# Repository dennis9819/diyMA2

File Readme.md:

# Modular MIDI-Controller for GrandMA2 Software
*** This project only allows you to controll the grandMA2 Software via a hardware controller. You sitll need to buy a henuine grandMA Interface to unlock the reqired amount of universes. Please also be aware, that this is just a side-project of mine and is not designed for production use. Use the real stuff for that.***

The diyMA is an open source MIDI controller, strongly mimicking the onPC command and fader wing layout. It communicates with the onPC Software via MIDI. This limits the resolution of the faders to 7-Bit (0-127). In my case this is still enough.
I've designed three modules to construct your own modular controller

## The Modules
### Module I : Fader-Module
The fader module contains:
* 5 Executor-Faders (+3 Buttons each)
* 5 Button Executor
* Controller-Header (to connect to Controller-Module)
* 2 PCBs (1x Component-PCB, 1x Panel-PCB)

### Module 3 : Controller-Module
The fader module contains:
* MIDI-In (Passed through for daisy chaining)
* MIDI-Out
* Atmega8-16P @ 16MHz
* 1 ICSP Header (programming)
* +5V/+12V Power Supply

### Module 3 : Fader-Module
The fader module contains:
* 1 Master-Fader
* 69 Buttons
* MIDI-In (Passed through for daisy chaining)
* MIDI-Out
* +5V/+12V Power Supply
* Atmega8-16P @ 16MHz
* 1 Expansion Header (e.g.: more Executors)
* 1 ICSP Header (programming)
* 2 PCBs (1x Component-PCB, 1x Panel-PCB)

## Special-Parts
* https://de.aliexpress.com/item/1005003752250659.html?spm=a2g0o.order_list.order_list_main.105.3a725c5fgOUOYA&gatewayAdapt=glo2deu
* https://de.aliexpress.com/item/1005003201365793.html?spm=a2g0o.order_list.order_list_main.336.3a725c5fgOUOYA&gatewayAdapt=glo2deu
* https://de.aliexpress.com/item/32913352658.html?spm=a2g0o.order_list.order_list_main.321.3a725c5fgOUOYA&gatewayAdapt=glo2deu

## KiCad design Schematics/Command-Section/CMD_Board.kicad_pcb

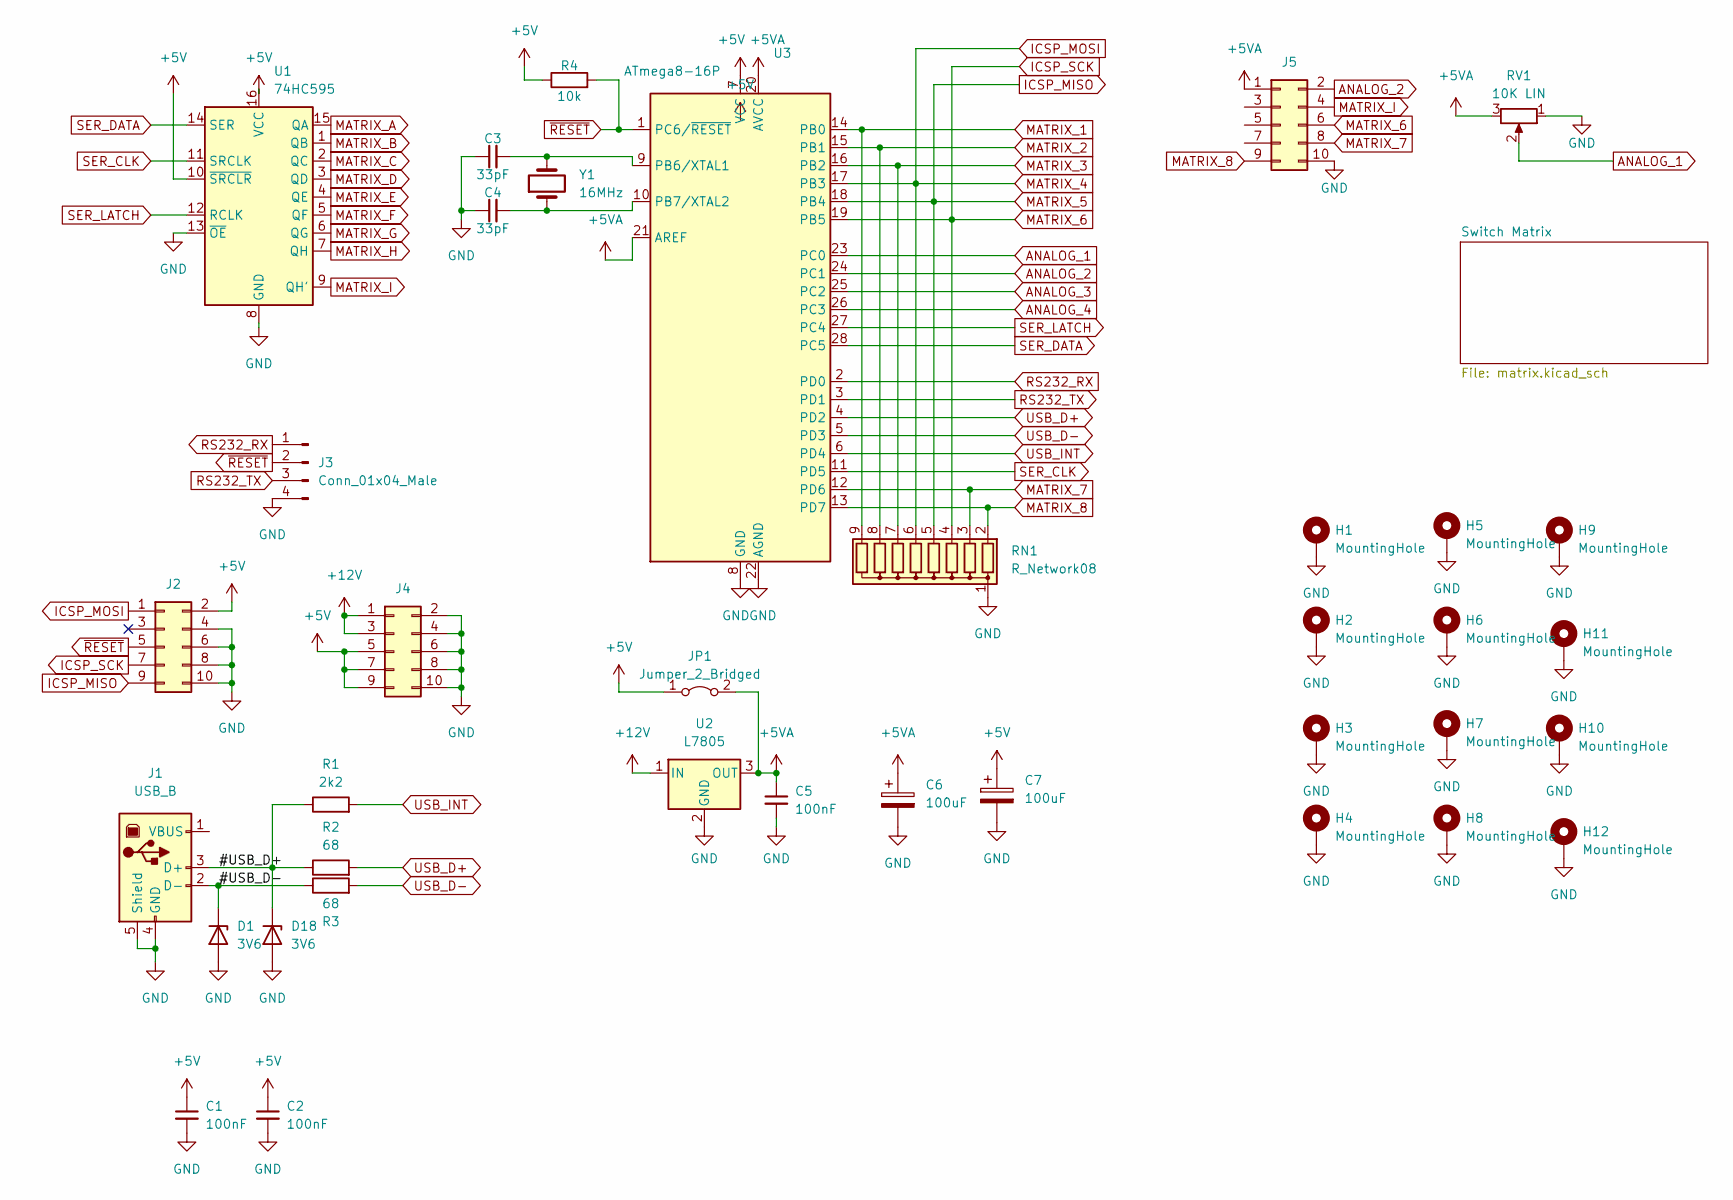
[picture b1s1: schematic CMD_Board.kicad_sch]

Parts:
C1, C2, C5: 100nF; C_Rect_L7.0mm_W2.0mm_P5.00mm
C3, C4: 33pF; C_Rect_L7.0mm_W2.0mm_P5.00mm
C6, C7: 100uF; CP_Radial_D8.0mm_P2.50mm
D1, D18: 3V6; D_DO-35_SOD27_P10.16mm_Horizontal
H1, H2, H3, H4, H5, H6, H7, H8, H9, H10, H11, H12: MountingHole; MountingHole_3.2mm_M3_DIN965_Pad
J1: USB_B; USB_B_Lumberg_2411_02_Horizontal
J2: Conn_02x05_Odd_Even; IDC-Header_2x05_P2.54mm_Vertical
J3: Conn_01x04_Male; JST_EH_B4B-EH-A_1x04_P2.50mm_Vertical
J4, J5: Conn_02x05_Odd_Even; IDC-Header_2x05_P2.54mm_Latch_Vertical
JP1: Jumper_2_Bridged; SolderJumper-2_P1.3mm_Bridged_Pad1.0x1.5mm
R1: 2k2; R_Axial_DIN0207_L6.3mm_D2.5mm_P7.62mm_Horizontal
R2, R3: 68; R_Axial_DIN0207_L6.3mm_D2.5mm_P7.62mm_Horizontal
R4: 10k; R_Axial_DIN0204_L3.6mm_D1.6mm_P2.54mm_Vertical
RN1: R_Network08; R_Array_SIP9
RV1: 10K LIN; RS60N12-LIN10K
U1: 74HC595; DIP-16_W7.62mm_Socket_LongPads
U2: L7805; TO-220-3_Horizontal_TabDown
U3: ATmega8-16P; DIP-28_W7.62mm_LongPads
Y1: 16MHz; Crystal_HC18-U_Vertical

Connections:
+5V: C1.1, C2.1, C7.1, J2.2, J4.5, J4.7, J4.9, JP1.1 (A), R4.1, U1.10 (~SRCLR), U1.16 (VCC), U3.7 (VCC)
+5VA: C5.1, C6.1, J5.1, JP1.2 (B), RV1.3, U2.3 (OUT), U3.20 (AVCC), U3.21 (AREF)
+12V: J4.1, J4.3, U2.1 (IN)
/#USB_D+: D18.1 (K), J1.3 (D+), R1.1, R2.1
/#USB_D-: D1.1 (K), J1.2 (D-), R3.1
ANALOG_1: RV1.2, U3.23 (PC0)
ANALOG_2: J5.2, U3.24 (PC1)
ANALOG_3: U3.25 (PC2)
ANALOG_4: U3.26 (PC3)
GND: C1.2, C2.2, C3.1, C4.1, C5.2, C6.2, C7.2, D1.2 (A), D18.2 (A), H1.1, H2.1, H3.1, H4.1, H5.1, H6.1, H7.1, H8.1, H9.1, H10.1, H11.1, H12.1, J1.4 (GND), J1.5 (Shield), J2.4, J2.6, J2.8, J2.10, J3.4, J4.2, J4.4, J4.6, J4.8, J4.10, J5.10, RN1.1 (common), RV1.1, U1.8 (GND), U1.13 (~OE), U2.2 (GND), U3.8 (GND), U3.22 (AGND); also elsewhere on the board
ICSP_MISO: J2.9, RN1.5 (R4), U3.18 (PB4); also elsewhere on the board
ICSP_MOSI: J2.1, RN1.6 (R5), U3.17 (PB3); also elsewhere on the board
ICSP_SCK: J2.7, J5.6, RN1.4 (R3), U3.19 (PB5); also elsewhere on the board
MATRIX_1: RN1.9 (R8), U3.14 (PB0); also elsewhere on the board
MATRIX_2: RN1.8 (R7), U3.15 (PB1); also elsewhere on the board
MATRIX_3: RN1.7 (R6), U3.16 (PB2); also elsewhere on the board
MATRIX_7: J5.8, RN1.3 (R2), U3.12 (PD6); also elsewhere on the board
MATRIX_8: J5.9, RN1.2 (R1), U3.13 (PD7); also elsewhere on the board
MATRIX_A: U1.15 (QA); also elsewhere on the board
MATRIX_B: U1.1 (QB); also elsewhere on the board
MATRIX_C: U1.2 (QC); also elsewhere on the board
MATRIX_D: U1.3 (QD); also elsewhere on the board
MATRIX_E: U1.4 (QE); also elsewhere on the board
MATRIX_F: U1.5 (QF); also elsewhere on the board
MATRIX_G: U1.6 (QG); also elsewhere on the board
MATRIX_H: U1.7 (QH); also elsewhere on the board
MATRIX_I: J5.4, U1.9 (QH'); also elsewhere on the board
unnamed: C3.2, U3.9 (PB6/XTAL1), Y1.2
unnamed: C4.2, U3.10 (PB7/XTAL2), Y1.1
RS232_RX: J3.1, U3.2 (PD0)
RS232_TX: J3.3, U3.3 (PD1)
SER_CLK: U1.11 (SRCLK), U3.11 (PD5)
SER_DATA: U1.14 (SER), U3.28 (PC5)
SER_LATCH: U1.12 (RCLK), U3.27 (PC4)
USB_D+: R2.2, U3.4 (PD2)
USB_D-: R3.2, U3.5 (PD3)
USB_INT: R1.2, U3.6 (PD4)
~RESET: J2.5, J3.2, R4.2, U3.1 (PC6/~RESET)

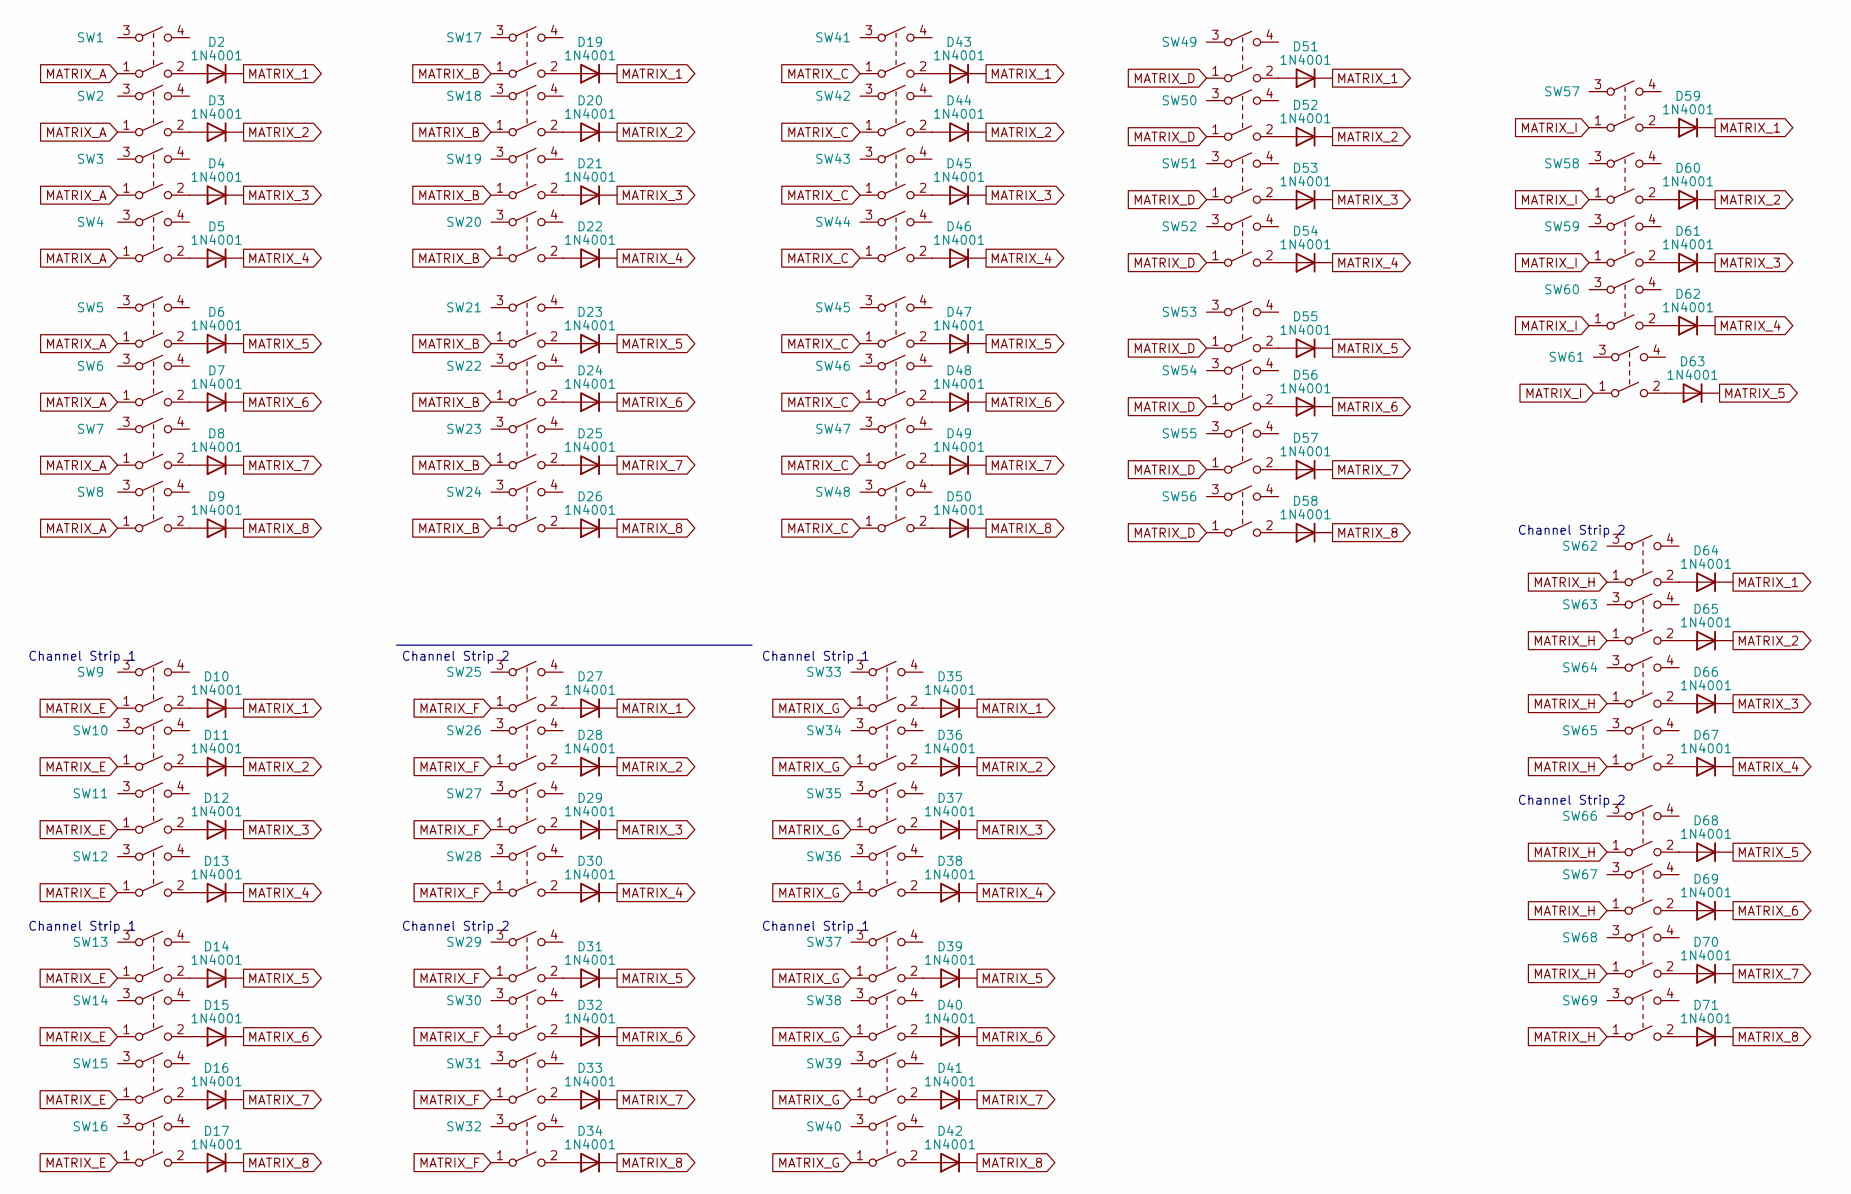
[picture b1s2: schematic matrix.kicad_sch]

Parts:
D2, D3, D4, D5, D6, D7, D8, D9, D10, D11, D12, D13, D14, D15, D16, D17, D19, D20, D21, D22, D23, D24, D25, D26, D27, D28, D29, D30, D31, D32, D33, D34, D35, D36, D37, D38, D39, D40, D41, D42, D43, D44, D45, D46, D47, D48, D49, D50, D51, D52, D53, D54, D55, D56, D57, D58, D59, D60, D61, D62, D63, D64, D65, D66, D67, D68, D69, D70, D71: 1N4001; D_DO-41_SOD81_P10.16mm_Horizontal
SW1, SW2, SW3, SW4, SW5, SW6, SW7, SW8, SW9, SW10, SW11, SW12, SW13, SW14, SW15, SW16, SW17, SW18, SW19, SW20, SW21, SW22, SW23, SW24, SW25, SW26, SW27, SW28, SW29, SW30, SW31, SW32, SW33, SW34, SW35, SW36, SW37, SW38, SW39, SW40, SW41, SW42, SW43, SW44, SW45, SW46, SW47, SW48, SW49, SW50, SW51, SW52, SW53, SW54, SW55, SW56, SW57, SW58, SW59, SW60, SW61, SW62, SW63, SW64, SW65, SW66, SW67, SW68, SW69: Switch_SW_DPST; SW_Cherry_MX_PCB_1.00u

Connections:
ICSP_MISO: D6.1 (K), D14.1 (K), D23.1 (K), D31.1 (K), D39.1 (K), D47.1 (K), D55.1 (K), D63.1 (K), D68.1 (K); also elsewhere on the board
ICSP_MOSI: D5.1 (K), D13.1 (K), D22.1 (K), D30.1 (K), D38.1 (K), D46.1 (K), D54.1 (K), D62.1 (K), D67.1 (K); also elsewhere on the board
ICSP_SCK: D7.1 (K), D15.1 (K), D24.1 (K), D32.1 (K), D40.1 (K), D48.1 (K), D56.1 (K), D69.1 (K); also elsewhere on the board
MATRIX_1: D2.1 (K), D10.1 (K), D19.1 (K), D27.1 (K), D35.1 (K), D43.1 (K), D51.1 (K), D59.1 (K), D64.1 (K); also elsewhere on the board
MATRIX_2: D3.1 (K), D11.1 (K), D20.1 (K), D28.1 (K), D36.1 (K), D44.1 (K), D52.1 (K), D60.1 (K), D65.1 (K); also elsewhere on the board
MATRIX_3: D4.1 (K), D12.1 (K), D21.1 (K), D29.1 (K), D37.1 (K), D45.1 (K), D53.1 (K), D61.1 (K), D66.1 (K); also elsewhere on the board
MATRIX_7: D8.1 (K), D16.1 (K), D25.1 (K), D33.1 (K), D41.1 (K), D49.1 (K), D57.1 (K), D70.1 (K); also elsewhere on the board
MATRIX_8: D9.1 (K), D17.1 (K), D26.1 (K), D34.1 (K), D42.1 (K), D50.1 (K), D58.1 (K), D71.1 (K); also elsewhere on the board
MATRIX_A: SW1.1, SW2.1, SW3.1, SW4.1, SW5.1, SW6.1, SW7.1, SW8.1; also elsewhere on the board
MATRIX_B: SW17.1, SW18.1, SW19.1, SW20.1, SW21.1, SW22.1, SW23.1, SW24.1; also elsewhere on the board
MATRIX_C: SW41.1, SW42.1, SW43.1, SW44.1, SW45.1, SW46.1, SW47.1, SW48.1; also elsewhere on the board
MATRIX_D: SW49.1, SW50.1, SW51.1, SW52.1, SW53.1, SW54.1, SW55.1, SW56.1; also elsewhere on the board
MATRIX_E: SW9.1, SW10.1, SW11.1, SW12.1, SW13.1, SW14.1, SW15.1, SW16.1; also elsewhere on the board
MATRIX_F: SW25.1, SW26.1, SW27.1, SW28.1, SW29.1, SW30.1, SW31.1, SW32.1; also elsewhere on the board
MATRIX_G: SW33.1, SW34.1, SW35.1, SW36.1, SW37.1, SW38.1, SW39.1, SW40.1; also elsewhere on the board
MATRIX_H: SW62.1, SW63.1, SW64.1, SW65.1, SW66.1, SW67.1, SW68.1, SW69.1; also elsewhere on the board
MATRIX_I: SW57.1, SW58.1, SW59.1, SW60.1, SW61.1; also elsewhere on the board
unnamed: D2.2 (A), SW1.2
unnamed: D3.2 (A), SW2.2
unnamed: D4.2 (A), SW3.2
unnamed: D5.2 (A), SW4.2
unnamed: D6.2 (A), SW5.2
unnamed: D7.2 (A), SW6.2
unnamed: D8.2 (A), SW7.2
unnamed: D9.2 (A), SW8.2
unnamed: D10.2 (A), SW9.2
unnamed: D11.2 (A), SW10.2
unnamed: D12.2 (A), SW11.2
unnamed: D13.2 (A), SW12.2
unnamed: D14.2 (A), SW13.2
unnamed: D15.2 (A), SW14.2
unnamed: D16.2 (A), SW15.2
unnamed: D17.2 (A), SW16.2
unnamed: D19.2 (A), SW17.2
unnamed: D20.2 (A), SW18.2
unnamed: D21.2 (A), SW19.2
unnamed: D22.2 (A), SW20.2
unnamed: D23.2 (A), SW21.2
unnamed: D24.2 (A), SW22.2
unnamed: D25.2 (A), SW23.2
unnamed: D26.2 (A), SW24.2
unnamed: D27.2 (A), SW25.2
unnamed: D28.2 (A), SW26.2
unnamed: D29.2 (A), SW27.2
unnamed: D30.2 (A), SW28.2
unnamed: D31.2 (A), SW29.2
unnamed: D32.2 (A), SW30.2
unnamed: D33.2 (A), SW31.2
unnamed: D34.2 (A), SW32.2
unnamed: D35.2 (A), SW33.2
unnamed: D36.2 (A), SW34.2
unnamed: D37.2 (A), SW35.2
unnamed: D38.2 (A), SW36.2
unnamed: D39.2 (A), SW37.2
unnamed: D40.2 (A), SW38.2
unnamed: D41.2 (A), SW39.2
unnamed: D42.2 (A), SW40.2
unnamed: D43.2 (A), SW41.2
unnamed: D44.2 (A), SW42.2
unnamed: D45.2 (A), SW43.2
unnamed: D46.2 (A), SW44.2
unnamed: D47.2 (A), SW45.2
unnamed: D48.2 (A), SW46.2
unnamed: D49.2 (A), SW47.2
unnamed: D50.2 (A), SW48.2
unnamed: D51.2 (A), SW49.2
unnamed: D52.2 (A), SW50.2
unnamed: D53.2 (A), SW51.2
unnamed: D54.2 (A), SW52.2
unnamed: D55.2 (A), SW53.2
unnamed: D56.2 (A), SW54.2
unnamed: D57.2 (A), SW55.2
unnamed: D58.2 (A), SW56.2
unnamed: D59.2 (A), SW57.2
unnamed: D60.2 (A), SW58.2
unnamed: D61.2 (A), SW59.2
unnamed: D62.2 (A), SW60.2
unnamed: D63.2 (A), SW61.2
unnamed: D64.2 (A), SW62.2
unnamed: D65.2 (A), SW63.2
unnamed: D66.2 (A), SW64.2
unnamed: D67.2 (A), SW65.2
unnamed: D68.2 (A), SW66.2
unnamed: D69.2 (A), SW67.2
unnamed: D70.2 (A), SW68.2
unnamed: D71.2 (A), SW69.2

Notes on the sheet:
Channel Strip 2
Channel Strip 1

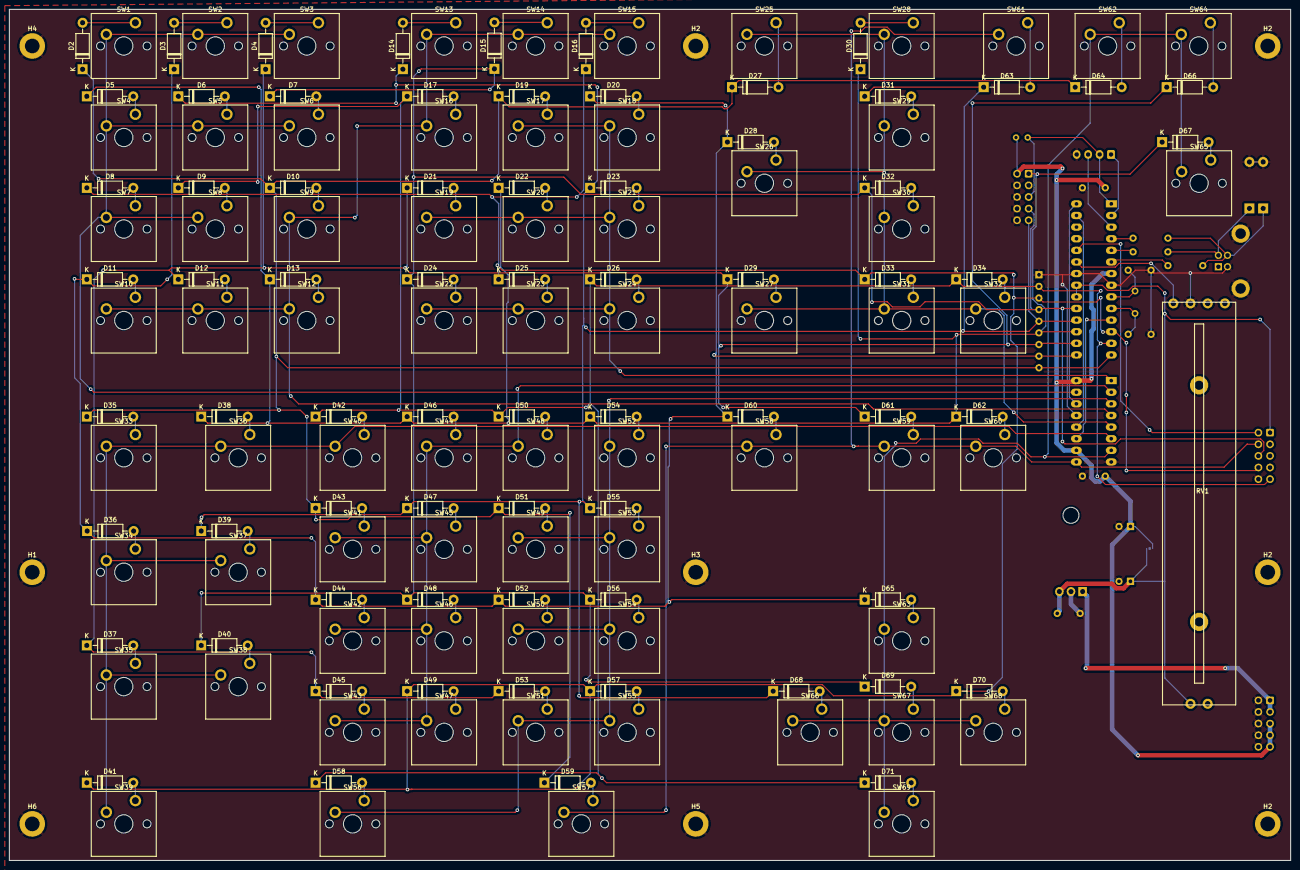
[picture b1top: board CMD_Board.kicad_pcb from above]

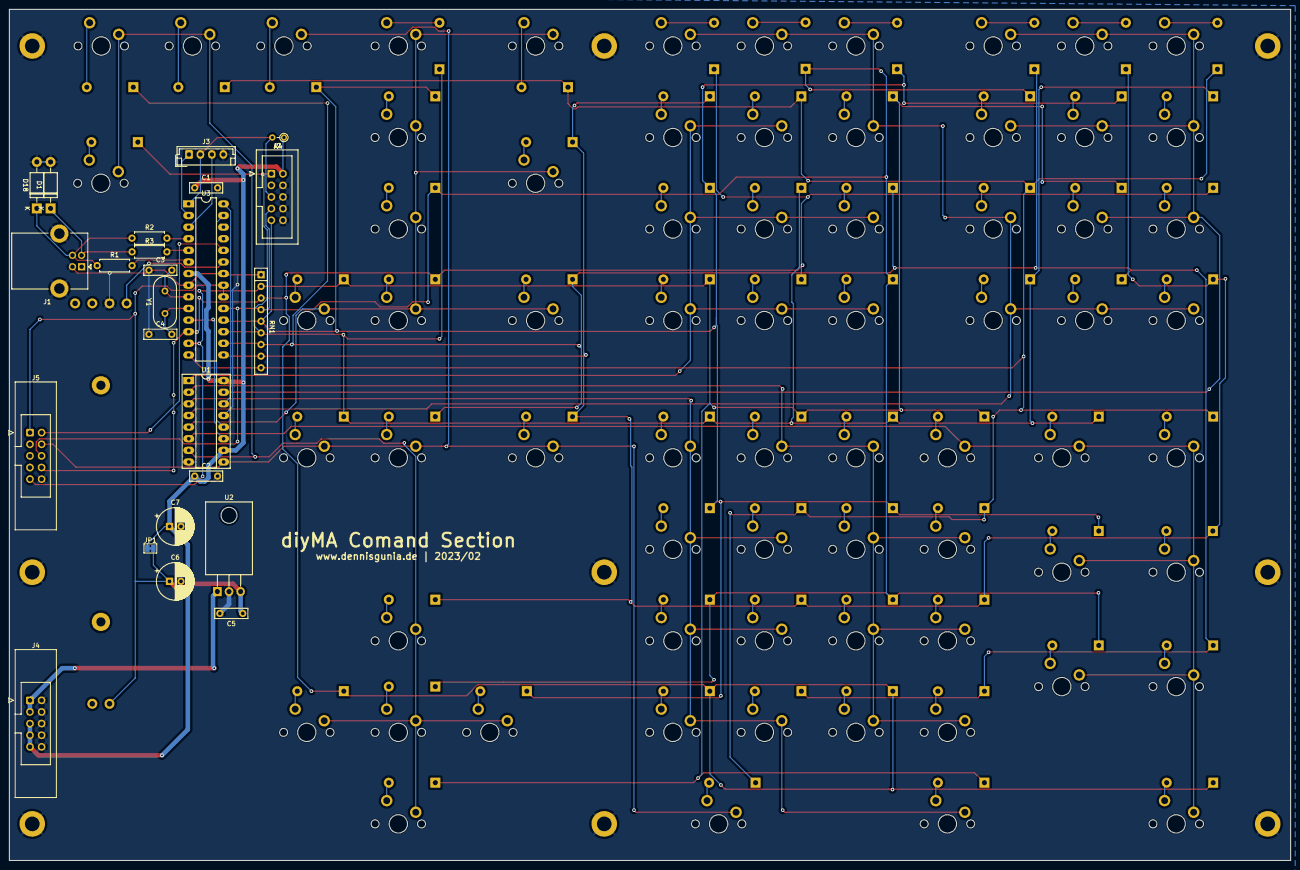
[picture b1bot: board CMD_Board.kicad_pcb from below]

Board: 2 copper layers, 280.0 x 186.0 mm, 172 parts (24 on the bottom side), 105 nets.

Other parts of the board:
H2#2, H2#3, H2#4: MountingHole; MountingHole_3.2mm_M3_DIN965_Pad

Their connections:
GND: H2#2.1, H2#3.1, H2#4.1; also elsewhere on the board

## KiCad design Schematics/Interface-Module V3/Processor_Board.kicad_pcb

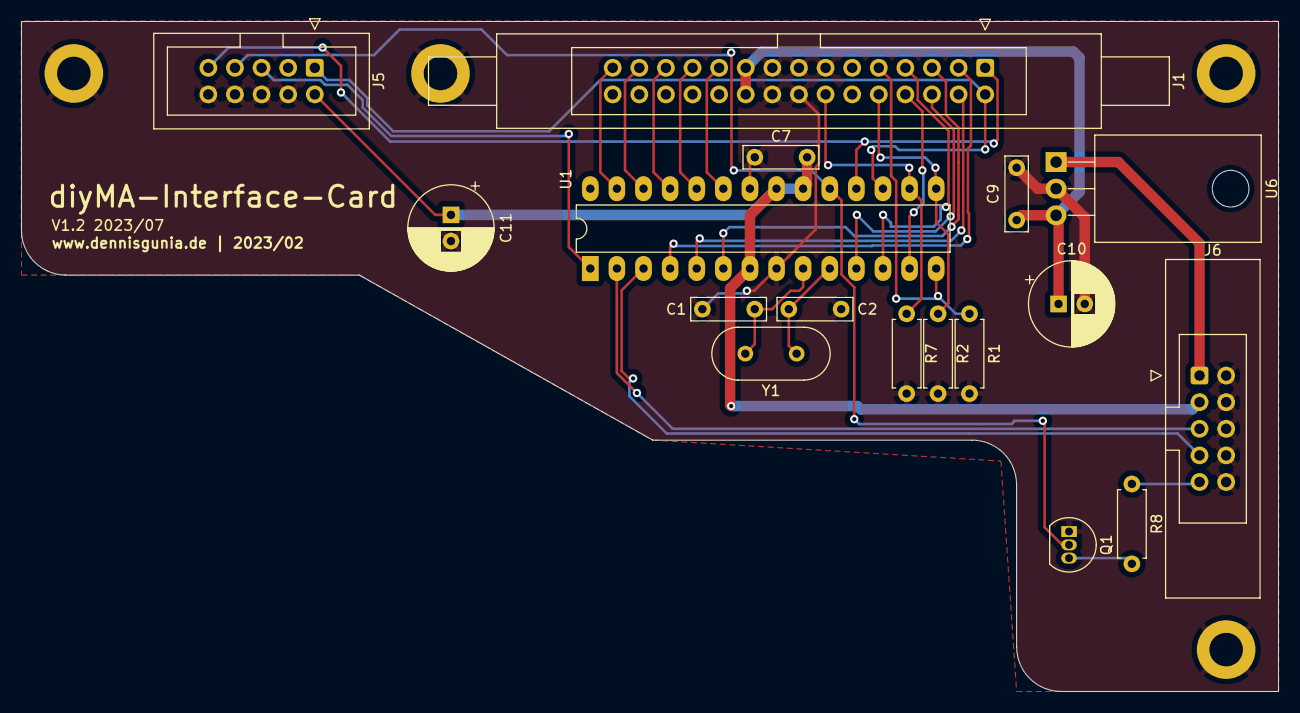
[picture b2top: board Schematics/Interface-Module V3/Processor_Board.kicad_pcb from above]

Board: 2 copper layers, 120.0 x 64.0 mm, 21 parts (0 on the bottom side), 28 nets.

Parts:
C1, C2: 33pF; C_Rect_L7.0mm_W2.0mm_P5.00mm
C7, C9: 100nF; C_Rect_L7.0mm_W2.0mm_P5.00mm
C10, C11: 100uF; CP_Radial_D8.0mm_P2.50mm
H4, H6, H6#2, H8: MountingHole; MountingHole_3.2mm_M3_DIN965_Pad
J1: Conn_02x16_Odd_Even; IDC-Header_2x15_P2.54mm_Latch6.5mm_Vertical
J5: Conn_02x05_Odd_Even; IDC-Header_2x05_P2.54mm_Vertical
J6: Conn_02x05_Odd_Even; IDC-Header_2x05_P2.54mm_Latch_Vertical
Q1: 2N3904; TO-92_Inline
R1, R2, R7: 10k; R_Axial_DIN0207_L6.3mm_D2.5mm_P7.62mm_Horizontal
R8: 100; R_Axial_DIN0207_L6.3mm_D2.5mm_P7.62mm_Horizontal
U1: ATmega8-16P; DIP-28_W7.62mm_LongPads
U6: L7805; TO-220-3_Horizontal_TabDown
Y1: 16MHz; Crystal_HC18-U_Vertical

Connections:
+5V: C7.1, C11.1, J5.2, J6.3, U1.7 (VCC), U1.20 (AVCC), U1.21 (AREF)
+5VA: C9.1, C10.1, J1.19, J1.20, U6.3 (OUT)
+12V: J6.1, U6.1 (IN)
ANALOG_11: J1.21, U1.23 (PC0)
ANALOG_12: J1.23, U1.24 (PC1)
ANALOG_13: J1.25, U1.25 (PC2)
ANALOG_14: J1.27, U1.26 (PC3)
ANALOG_15: J1.29, U1.27 (PC4)
GND: C1.1, C2.1, C7.2, C9.2, C10.2, C11.2, H4.1, H6.1, H6#2.1, H8.1, J1.13, J1.15, J1.16, J1.17, J1.18, J1.22, J1.24, J1.26, J1.28, J1.30, J5.4, J5.6, J5.8, J5.10, J6.2, J6.4, J6.6, J6.8, J6.10, Q1.1 (E), R1.2, R2.2, R7.2, U1.8 (GND), U1.22 (AGND), U6.2 (GND)
ICSP2_MISO: J1.1, J5.9, U1.18 (PB4)
ICSP2_MOSI: J1.2, J5.1, U1.17 (PB3)
ICSP2_SCK: J5.7, Q1.2 (B), U1.19 (PB5)
MATRIX_3: J1.3, U1.4 (PD2)
MATRIX_4: J1.4, U1.5 (PD3)
MATRIX_5: J1.5, U1.6 (PD4)
MATRIX_6: J1.6, U1.11 (PD5)
MATRIX_7: J1.7, U1.12 (PD6)
MATRIX_8: J1.8, U1.13 (PD7)
MATRIX_A: J1.9, R1.1, U1.14 (PB0)
MATRIX_B: J1.10, R2.1, U1.15 (PB1)
MATRIX_C: J1.14, R7.1, U1.16 (PB2)
unnamed: Q1.3 (C), R8.2
unnamed: C1.2, U1.9 (PB6/XTAL1), Y1.2
unnamed: C2.2, U1.10 (PB7/XTAL2), Y1.1
RX: J6.7, U1.3 (PD1)
TX: J6.5, U1.2 (PD0)
\EVNT: J6.9, R8.1
~RESET: J5.5, U1.1 (PC6/~RESET)

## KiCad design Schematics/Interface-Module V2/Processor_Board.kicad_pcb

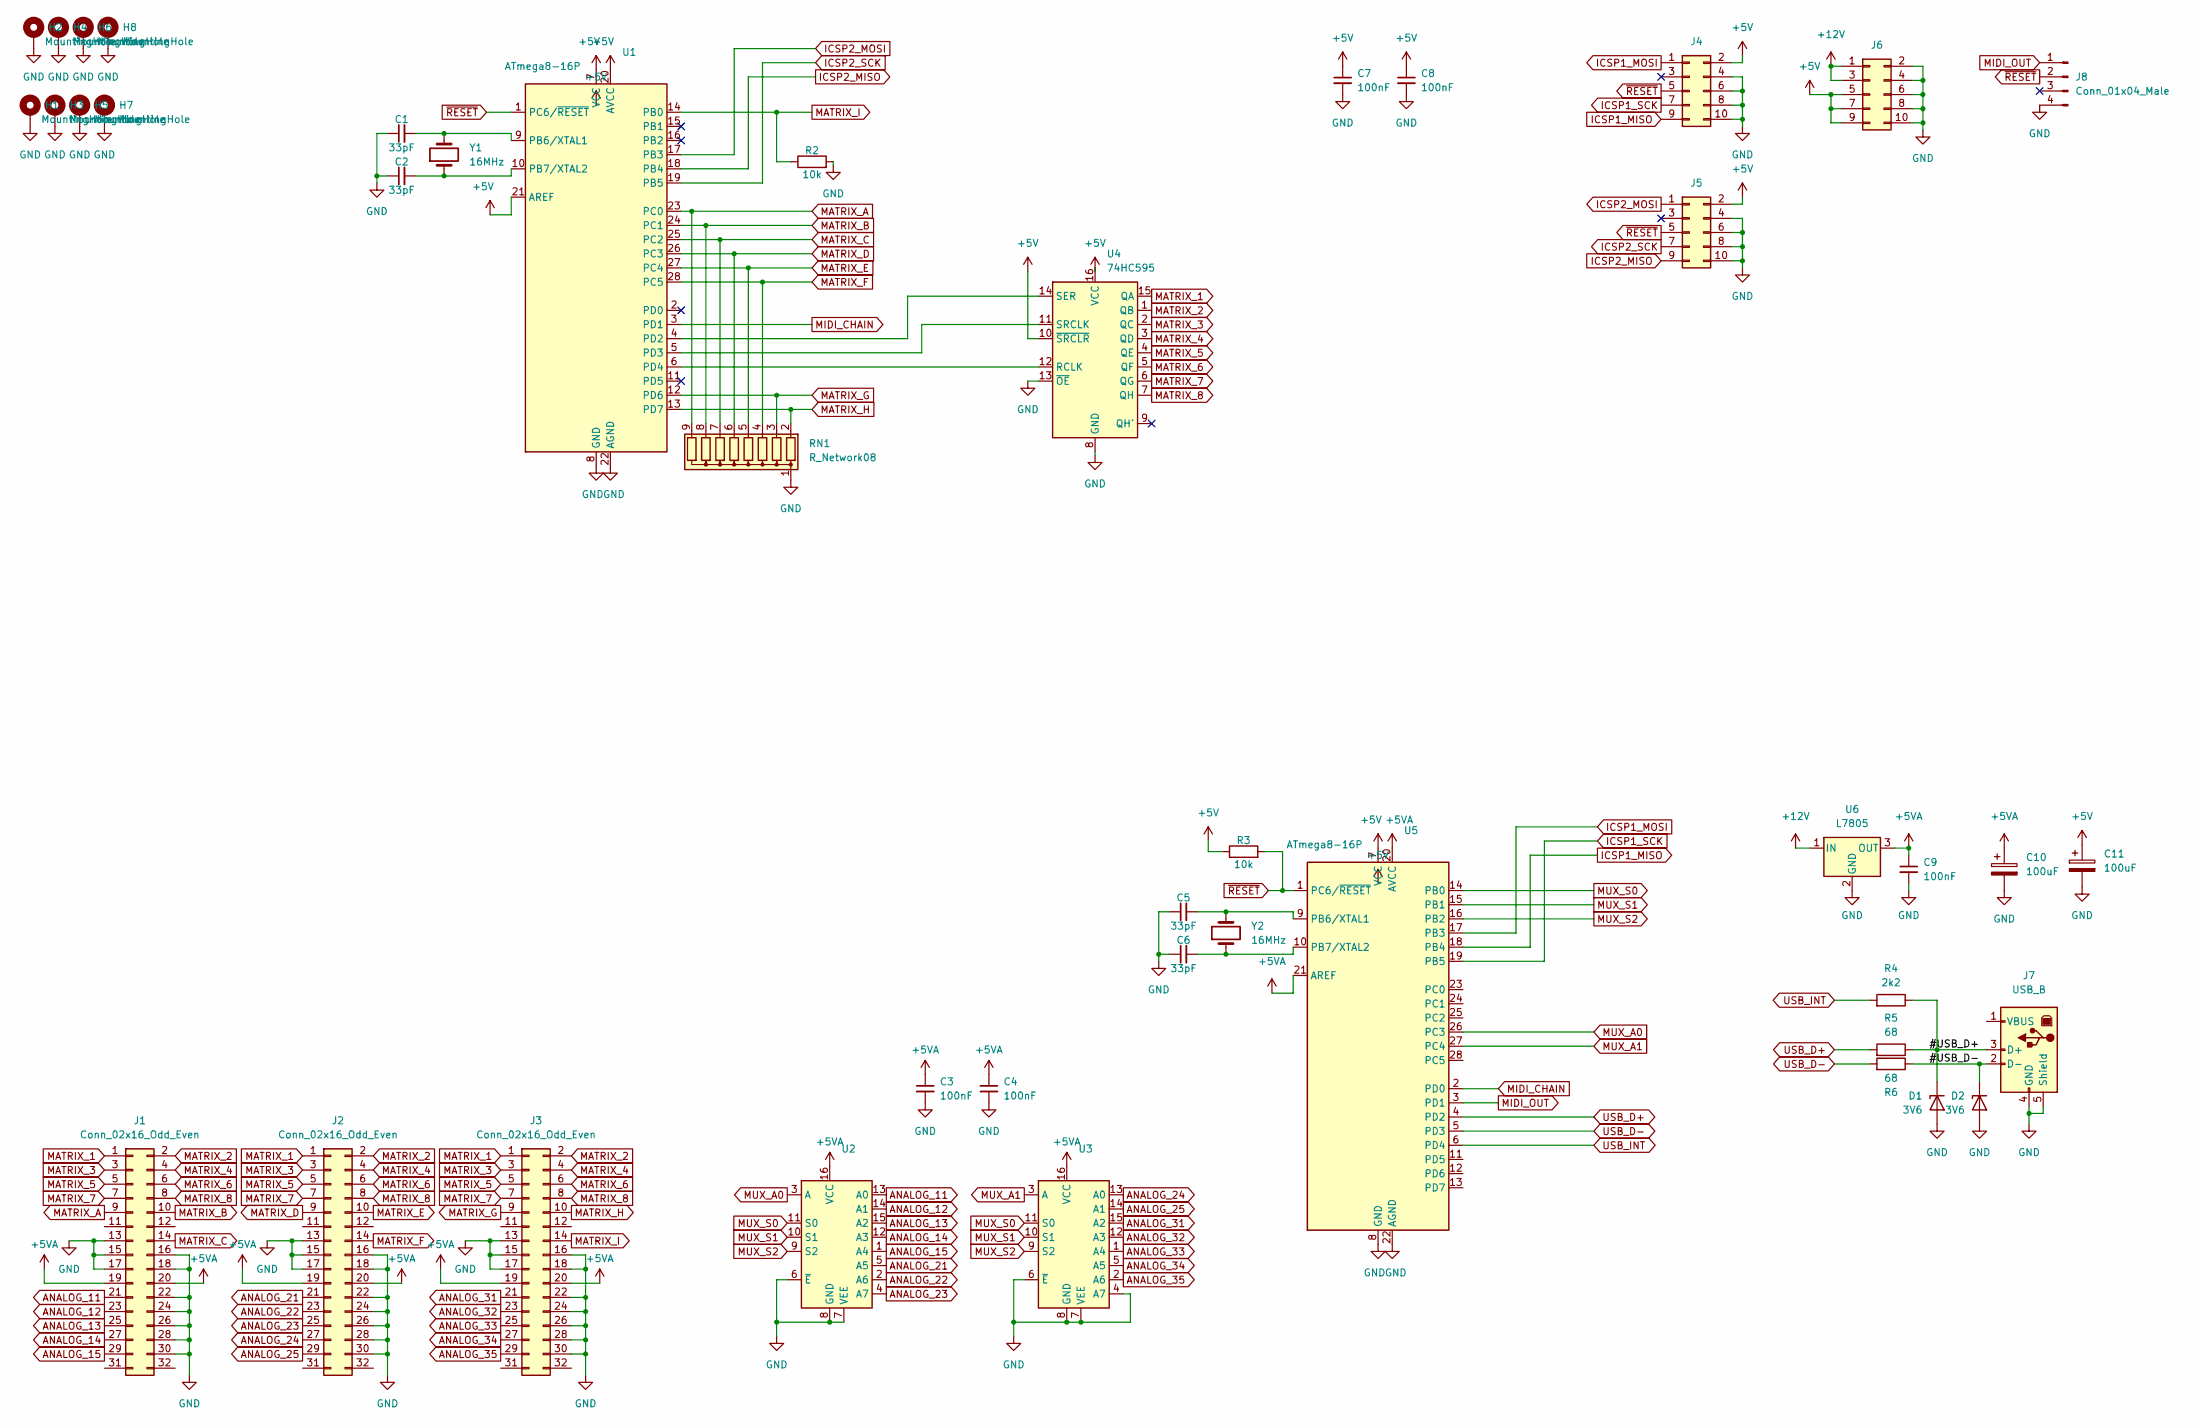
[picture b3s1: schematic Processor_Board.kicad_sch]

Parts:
C1, C2, C5, C6: 33pF; C_Rect_L7.0mm_W2.0mm_P5.00mm
C3, C4, C7, C8, C9: 100nF; C_Rect_L7.0mm_W2.0mm_P5.00mm
C10, C11: 100uF; CP_Radial_D8.0mm_P2.50mm
D1, D2: 3V6; D_DO-35_SOD27_P10.16mm_Horizontal
H1, H2, H3, H4, H5, H6, H7, H8: MountingHole; MountingHole_3.2mm_M3_DIN965_Pad
J1, J2, J3: Conn_02x16_Odd_Even; IDC-Header_2x15_P2.54mm_Latch6.5mm_Vertical
J4, J5: Conn_02x05_Odd_Even; IDC-Header_2x05_P2.54mm_Vertical
J6: Conn_02x05_Odd_Even; IDC-Header_2x05_P2.54mm_Latch_Vertical
J7: USB_B; USB_B_Lumberg_2411_02_Horizontal
J8: Conn_01x04_Male; JST_EH_B4B-EH-A_1x04_P2.50mm_Vertical
R2, R3: 10k; R_Axial_DIN0204_L3.6mm_D1.6mm_P2.54mm_Vertical
R4: 2k2; R_Axial_DIN0207_L6.3mm_D2.5mm_P7.62mm_Horizontal
R5, R6: 68; R_Axial_DIN0207_L6.3mm_D2.5mm_P7.62mm_Horizontal
RN1: R_Network08; R_Array_SIP9
U1, U5: ATmega8-16P; DIP-28_W7.62mm_LongPads
U2, U3: (no value)
U4: 74HC595; DIP-16_W10.16mm_LongPads
U6: L7805; TO-220-3_Horizontal_TabDown
Y1, Y2: 16MHz; Crystal_HC18-U_Vertical

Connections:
+5V: C7.1, C8.1, C11.1, J4.2, J5.2, J6.5, J6.7, J6.9, R3.1, U1.7 (VCC), U1.20 (AVCC), U1.21 (AREF), U4.10 (~SRCLR), U4.16 (VCC), U5.7 (VCC)
+5VA: C3.1, C4.1, C9.1, C10.1, J1.19, J1.20, J2.19, J2.20, J3.19, J3.20, U2.16 (VCC), U3.16 (VCC), U5.20 (AVCC), U5.21 (AREF), U6.3 (OUT)
+12V: J6.1, J6.3, U6.1 (IN)
/#USB_D+: D1.1 (K), J7.3 (D+), R4.1, R5.1
/#USB_D-: D2.1 (K), J7.2 (D-), R6.1
ANALOG_11: J1.21, U2.13 (A0)
ANALOG_12: J1.23, U2.14 (A1)
ANALOG_13: J1.25, U2.15 (A2)
ANALOG_14: J1.27, U2.12 (A3)
ANALOG_15: J1.29, U2.1 (A4)
ANALOG_21: J2.21, U2.5 (A5)
ANALOG_22: J2.23, U2.2 (A6)
ANALOG_23: J2.25, U2.4 (A7)
ANALOG_24: J2.27, U3.13 (A0)
ANALOG_25: J2.29, U3.14 (A1)
ANALOG_31: J3.21, U3.15 (A2)
ANALOG_32: J3.23, U3.12 (A3)
ANALOG_33: J3.25, U3.1 (A4)
ANALOG_34: J3.27, U3.5 (A5)
ANALOG_35: J3.29, U3.2 (A6)
GND: C1.1, C2.1, C3.2, C4.2, C5.1, C6.1, C7.2, C8.2, C9.2, C10.2, C11.2, D1.2 (A), D2.2 (A), H1.1, H2.1, H3.1, H4.1, H5.1, H6.1, H7.1, H8.1, J1.13, J1.15, J1.16, J1.17, J1.18, J1.22, J1.24, J1.26, J1.28, J1.30, J2.13, J2.15, J2.16, J2.17, J2.18, J2.22, J2.24, J2.26, J2.28, J2.30, J3.13, J3.15, J3.16, J3.17, J3.18, J3.22, J3.24, J3.26, J3.28, J3.30, J4.4, J4.6, J4.8, J4.10, J5.4, J5.6, J5.8, J5.10, J6.2, J6.4, J6.6, J6.8, J6.10, J7.4 (GND), J7.5 (Shield), J8.4, R2.2, RN1.1 (common), U1.8 (GND), U1.22 (AGND), U2.6 (~E), U2.7 (VEE), U2.8 (GND), U3.4 (A7), U3.6 (~E), U3.7 (VEE), U3.8 (GND), U4.8 (GND), U4.13 (~OE), U5.8 (GND), U5.22 (AGND), U6.2 (GND)
ICSP1_MISO: J4.9, U5.18 (PB4)
ICSP1_MOSI: J4.1, U5.17 (PB3)
ICSP1_SCK: J4.7, U5.19 (PB5)
ICSP2_MISO: J5.9, U1.18 (PB4)
ICSP2_MOSI: J5.1, U1.17 (PB3)
ICSP2_SCK: J5.7, U1.19 (PB5)
MATRIX_1: J1.1, J2.1, J3.1, U4.15 (QA)
MATRIX_2: J1.2, J2.2, J3.2, U4.1 (QB)
MATRIX_3: J1.3, J2.3, J3.3, U4.2 (QC)
MATRIX_4: J1.4, J2.4, J3.4, U4.3 (QD)
MATRIX_5: J1.5, J2.5, J3.5, U4.4 (QE)
MATRIX_6: J1.6, J2.6, J3.6, U4.5 (QF)
MATRIX_7: J1.7, J2.7, J3.7, U4.6 (QG)
MATRIX_8: J1.8, J2.8, J3.8, U4.7 (QH)
MATRIX_A: J1.9, RN1.9 (R8), U1.23 (PC0)
MATRIX_B: J1.10, RN1.8 (R7), U1.24 (PC1)
MATRIX_C: J1.14, RN1.7 (R6), U1.25 (PC2)
MATRIX_D: J2.9, RN1.6 (R5), U1.26 (PC3)
MATRIX_E: J2.10, RN1.5 (R4), U1.27 (PC4)
MATRIX_F: J2.14, RN1.4 (R3), U1.28 (PC5)
MATRIX_G: J3.9, RN1.3 (R2), U1.12 (PD6)
MATRIX_H: J3.10, RN1.2 (R1), U1.13 (PD7)
MATRIX_I: J3.14, R2.1, U1.14 (PB0)
MIDI_CHAIN: U1.3 (PD1), U5.2 (PD0)
MIDI_OUT: J8.1, U5.3 (PD1)
MUX_A0: U2.3 (A), U5.26 (PC3)
MUX_A1: U3.3 (A), U5.27 (PC4)
MUX_S0: U2.11 (S0), U3.11 (S0), U5.14 (PB0)
MUX_S1: U2.10 (S1), U3.10 (S1), U5.15 (PB1)
MUX_S2: U2.9 (S2), U3.9 (S2), U5.16 (PB2)
unnamed: C1.2, U1.9 (PB6/XTAL1), Y1.2
unnamed: C2.2, U1.10 (PB7/XTAL2), Y1.1
unnamed: C5.2, U5.9 (PB6/XTAL1), Y2.2
unnamed: C6.2, U5.10 (PB7/XTAL2), Y2.1
unnamed: U1.5 (PD3), U4.11 (SRCLK)
unnamed: U1.6 (PD4), U4.12 (RCLK)
unnamed: U1.4 (PD2), U4.14 (SER)
USB_D+: R5.2, U5.4 (PD2)
USB_D-: R6.2, U5.5 (PD3)
USB_INT: R4.2, U5.6 (PD4)
~RESET: J4.5, J5.5, J8.2, R3.2, U1.1 (PC6/~RESET), U5.1 (PC6/~RESET)

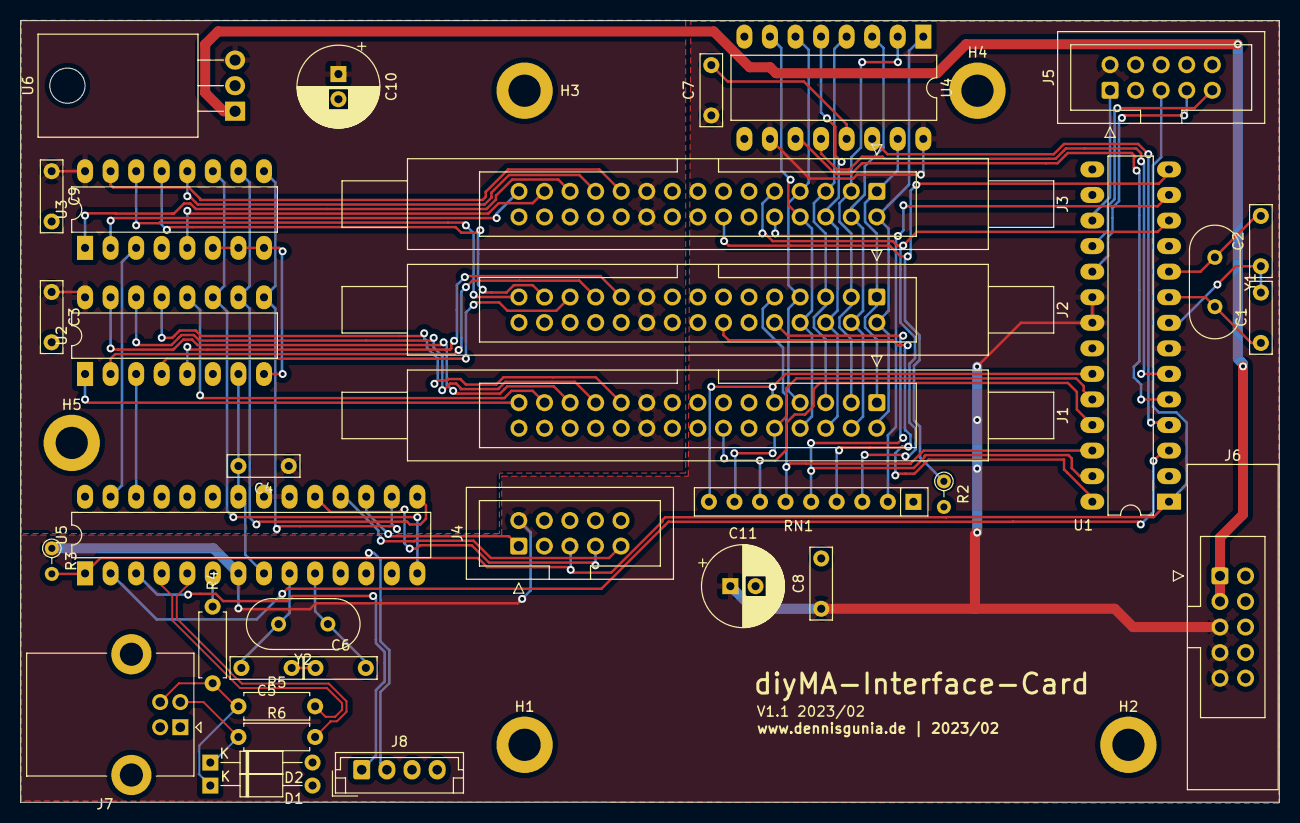
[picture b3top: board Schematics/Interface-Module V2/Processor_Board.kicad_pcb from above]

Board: 2 copper layers, 125.1 x 77.7 mm, 40 parts (0 on the bottom side), 62 nets.

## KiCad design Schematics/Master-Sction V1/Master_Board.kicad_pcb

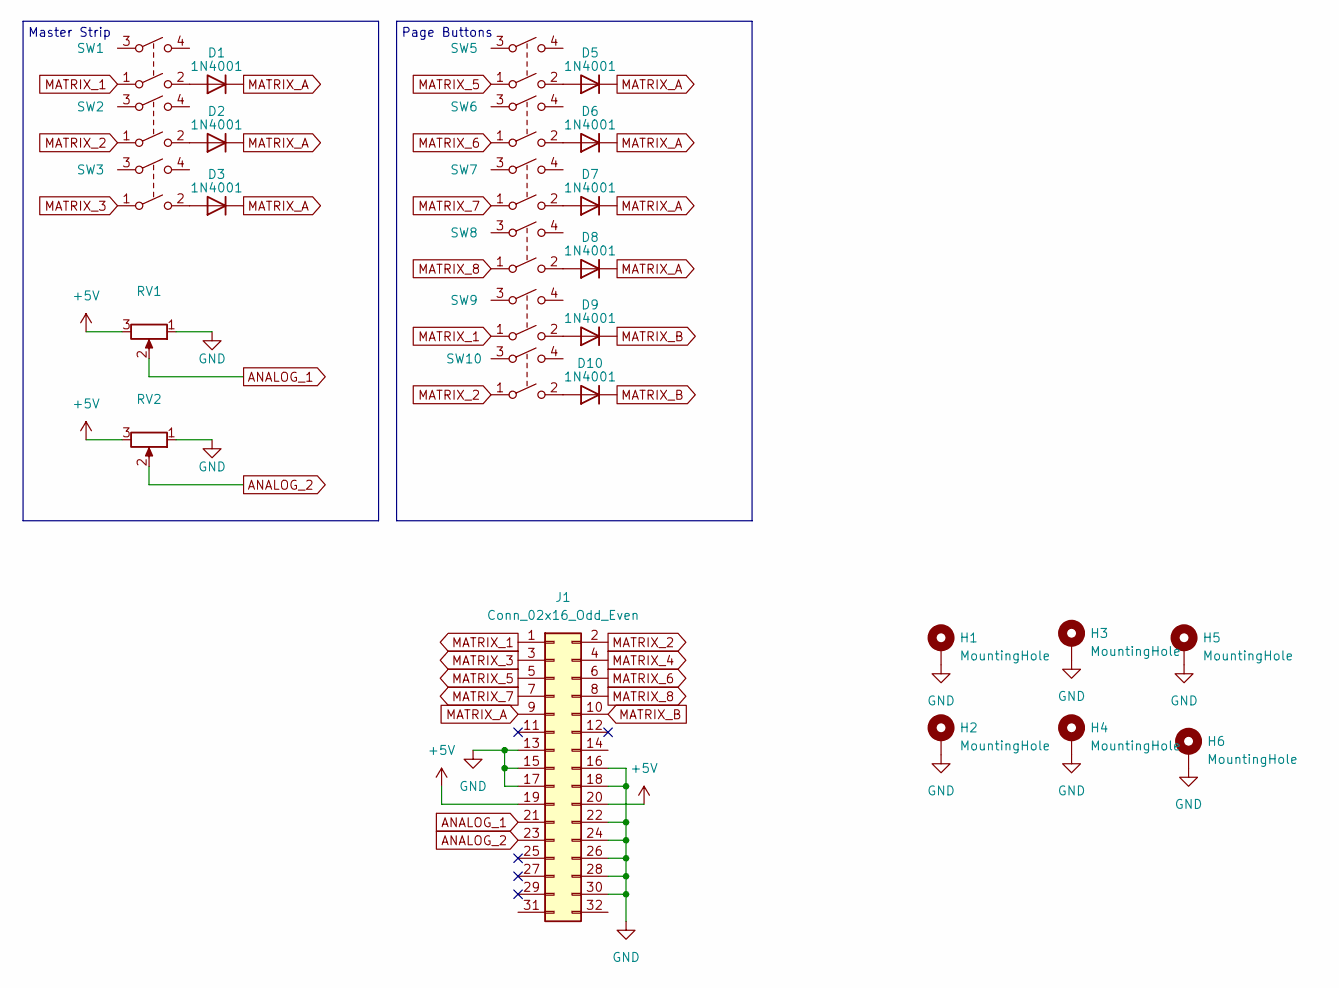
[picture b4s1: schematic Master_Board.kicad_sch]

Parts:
D1, D2, D3, D5, D6, D7, D8, D9, D10: 1N4001; D_DO-41_SOD81_P10.16mm_Horizontal
H1, H2, H3, H4, H5, H6: MountingHole; MountingHole_3.2mm_M3_DIN965_Pad
J1: Conn_02x16_Odd_Even; IDC-Header_2x15_P2.54mm_Latch6.5mm_Vertical
RV1, RV2: (no value)
SW1, SW2, SW3: (no value)
SW5, SW6, SW7, SW8, SW9, SW10: Switch_SW_DPST; SW_Cherry_MX_PCB_1.00u

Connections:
+5V: J1.19, J1.20, RV1.3, RV2.3
ANALOG_1: J1.21, RV1.2
ANALOG_2: J1.23, RV2.2
GND: H1.1, H2.1, H3.1, H4.1, H5.1, H6.1, J1.13, J1.15, J1.16, J1.17, J1.18, J1.22, J1.24, J1.26, J1.28, J1.30, RV1.1, RV2.1
MATRIX_1: J1.1, SW1.1, SW9.1
MATRIX_2: J1.2, SW2.1, SW10.1
MATRIX_3: J1.3, SW3.1
MATRIX_4: J1.4
MATRIX_5: J1.5, SW5.1
MATRIX_6: J1.6, SW6.1
MATRIX_7: J1.7, SW7.1
MATRIX_8: J1.8, SW8.1
MATRIX_A: D1.1 (K), D2.1 (K), D3.1 (K), D5.1 (K), D6.1 (K), D7.1 (K), D8.1 (K), J1.9
MATRIX_B: D9.1 (K), D10.1 (K), J1.10
unnamed: D1.2 (A), SW1.2
unnamed: D2.2 (A), SW2.2
unnamed: D3.2 (A), SW3.2
unnamed: D5.2 (A), SW5.2
unnamed: D6.2 (A), SW6.2
unnamed: D7.2 (A), SW7.2
unnamed: D8.2 (A), SW8.2
unnamed: D9.2 (A), SW9.2
unnamed: D10.2 (A), SW10.2

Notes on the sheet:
Page Buttons
Master Strip
